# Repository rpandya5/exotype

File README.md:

# Exotype: Intraoral Assistive Speech Device with AR Interface

## Project Overview
Exotype is an assistive speech wearable device combining an intraoral interface with AR-enhanced visual feedback for individuals with severe speech disabilities. This system enables intuitive text input through tongue movements and EMG-based bite detection. This was developed at Founders Inc (San Francisco) as part of the University Residency Program.

Thank you to Merge Grants and 1517's Medici Project for supporting this project!

*This project is still being developed. All files may not be up to date.*

## Demo & Hardware
<div align="center">
  <table>
    <tr>
      <td align="center" width="50%">
        
        <br>
        <em>Project Demo Video</em>
      </td>
      <td align="center" width="50%">
        
        <br>
        <em>Exotype Prototype</em>
      </td>
    </tr>
  </table>
</div>

## Technical Specifications

### Intraoral Interface
- Input Mechanism: Analog thumbstick (Adafruit SWITCH THUMBSTICK PUCK #2765)
  - Dual 10kΩ potentiometer configuration
  - Self-centering mechanism
  - Dimensions: 17.5mm × 17.4mm × 12.0mm
  - X/Y axis voltage output proportional to deflection

### EMG Bite Detection
- Sensor: MyoWare® 2.0 Muscle Sensor
  - Operating Voltage: 2.27V-5.47V (typical 3.3V-5V)
  - Input Bias Current: 250pA (max 1nA)
  - Form Factor: 37.57mm × 35.90mm
  - Triple output modes: Raw EMG/Rectified/Envelope
  - Cheek-mounted electrode configuration
  - Adjustable gain for sensitivity tuning

### Microcontroller System
- Platform: Seeed Studio XIAO ESP32C3
  - Built-in ADC for potentiometer signal processing
  - Bluetooth connectivity for AR glasses interface
  - Power Management:
    - 3.7V LiPo battery configuration
    - Step-up converter

### Visual Interface
- Display: VUF-110 Wearable Display
  - Physical Display: 0.195"
  - Virtual Screen: 4" at 12" viewing distance
  - Resolution: 720p HDMI input
  - Refresh Rate: 60Hz
  - Power: Internal battery (90-minute runtime)
  - Charging: 5V Micro USB
  - Mounting: Magnetic docking system

## PCB Design Specifications
Custom flexible PCB design optimized for intraoral placement:
- Manufacturer Specifications:
  - Single layer polyimide flex construction
  - Thickness: 0.13mm
  - Dimensions: 250mm × 62mm
  - Copper Weight: 0.5oz (18μm)
  - Surface Finish: ENIG (2U")
  - Track/Spacing: ≥0.06mm
  - Minimum Hole Size: ≥φ0.15/0.35mm
  - Coverlay: Black with white silkscreen

<table>
  <tr>
    <td align="center" width="50%">
      
      <br>
      <em>PCB Schematic</em>
    </td>
    <td align="center" width="50%">
      
      <br>
      <em>PCB Layout</em>
    </td>
  </tr>
</table>

## System Architecture & Operation Cycle

### Signal Flow & Processing Pipeline

#### 1. Input Acquisition

**Joystick Processing:**
- Dual 10kΩ potentiometers generate analog voltage signals (0-3.3V) corresponding to X/Y positions
- ESP32C3's integrated 12-bit ADC samples each axis:
  - ADC1 Channel 0: X-axis position
  - ADC1 Channel 1: Y-axis position
- Sampling rate: 100Hz per channel
- Resolution: 4096 discrete positions (12-bit)
- Built-in voltage reference for stable measurements

**EMG Signal Processing:**
- MyoWare 2.0 sensor captures muscle activation during bite events
- Rectified EMG signal processed through envelope detection
- Analog output fed into ESP32C3 ADC Channel 2
- Signal conditioning:
  - Hardware gain adjustment on MyoWare board
  - Digital threshold filtering for bite detection
  - Debouncing to prevent false triggers

#### 2. Power Management
- 3.7V 500mAh LiPo battery
- Voltage monitoring via ESP32C3 ADC
- Power distribution:
  - ESP32C3: 3.3V operating voltage
  - Joystick potentiometers: 3.3V reference
  - EMG sensor: 3.3V regulated supply

#### 3. Data Processing & Communication

**Microcontroller Operations:**
- ESP32C3 core functions:
  - ADC sampling management
  - Digital filtering of input signals
  - Coordinate mapping for cursor position
  - Bluetooth packet formation and transmission
  - Power state management

**Bluetooth Communication Protocol:**
- BLE 5.0 implementation
- Custom GATT service for device communication
- Packet structure:
```
{
  timestamp: uint32,
  x_pos: uint12,
  y_pos: uint12,
  bite_state: bool,
  battery_level: uint8
}
```
- Transmission rate: 50Hz
- Error checking and packet validation
- Auto-reconnection handling

#### 4. Visual Interface System

**Display Processing:**
- HDMI signal generation (720p @ 60Hz)
- Virtual keyboard overlay:
  - Resolution: 1280x720
  - Dynamic keyboard layout adaptation
  - Visual feedback for cursor position
  - Character highlighting on hover

**Cursor Control System:**
- Non-linear acceleration mapping for precise control
- Coordinate transformation:
```
x_screen = f(x_joystick) * screen_width
y_screen = f(y_joystick) * screen_height
```
where f(x) implements smooth acceleration curve

#### 5. Text Input & Processing

**Selection System:**
- Character selection confirmation delay: 50ms
- Double-bite detection for special functions

**Text Prediction Engine:**
- N-gram based prediction model
- Personal dictionary integration
- Context-aware suggestions
- Update frequency: Real-time on character input

<p align="center">
  
  <br>
  <em>Keyboard display on AR Glasses</em>
</p>

### Data Flow Diagram
```mermaid
graph TD
    A[Joystick Input] -->|Analog Voltage| B[ADC Conversion]
    C[EMG Sensor] -->|Envelope Signal| B
    B --> D[ESP32C3 Processing]
    D -->|BLE Protocol| E[Display System]
    D -->|Power Management| F[Battery Monitor]
    E --> G[Keyboard Overlay]
    E --> H[Text Prediction]
    G --> I[Visual Feedback]
    H --> I
```

## Future Development Roadmap
1. Integration with Brilliant Labs' Frame AR glasses
2. Capacitive touch sensor implementation
3. Custom AR glasses development
4. Enhanced predictive text algorithms
5. Extended battery life optimizations

## Repository Structure
```
├── firmware/
│   ├── src/
│   │   ├── main.cpp
│   │   ├── mouse_control.py
│   │   └── test.py
│   └── platformio.ini
├── hardware/
│   ├── pcb/
│   │   ├── gerbers/
│   │   └── kicad_files/
│   └── ar-glasses/ (to be completed)
├── software/
    ├── t_complete.py
    └── t_keyboard.py

```

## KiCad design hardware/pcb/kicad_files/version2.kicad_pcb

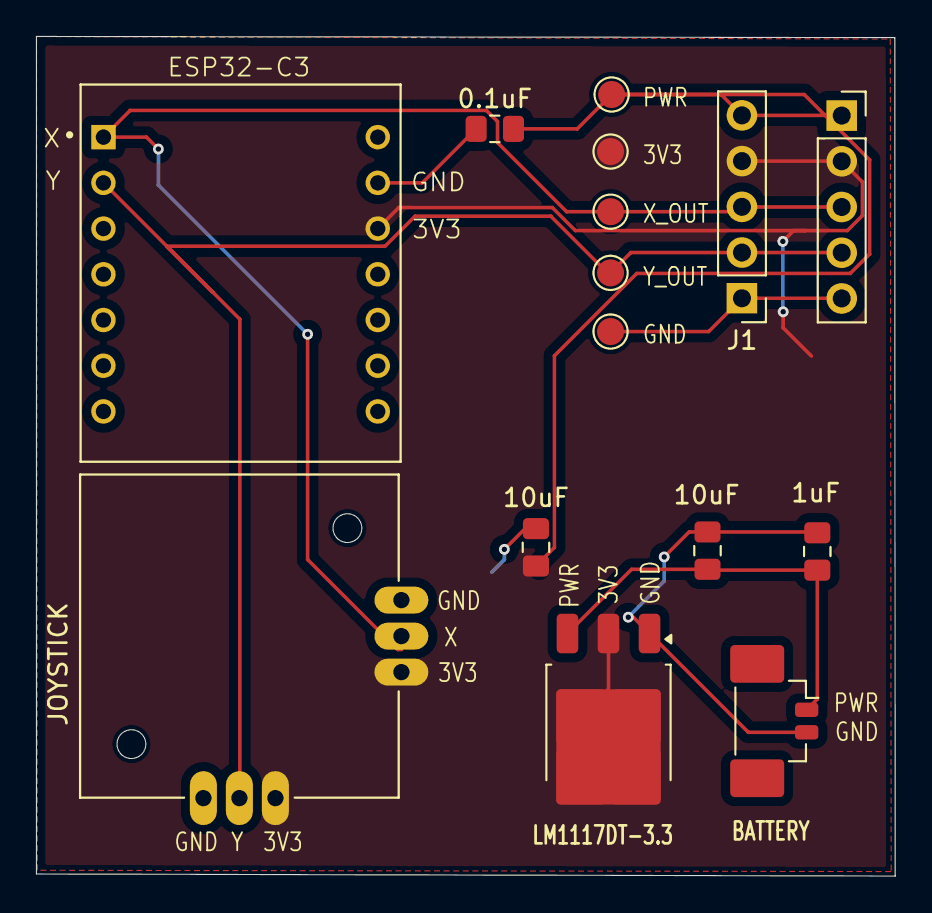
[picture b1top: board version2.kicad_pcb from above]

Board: 2 copper layers, 47.7 x 46.6 mm, 15 parts (0 on the bottom side), 5 nets.

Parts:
BATTERY: BATTERY; Molex_PicoBlade_53398-0271_1x02-1MP_P1.25mm_Vertical
C1: 1uF; C_0805_2012Metric_Pad1.18x1.45mm_HandSolder
C2, C3: 10uF; C_0805_2012Metric_Pad1.18x1.45mm_HandSolder
C4: 0.1uF; C_0805_2012Metric_Pad1.18x1.45mm_HandSolder
J1: Conn_01x05_Pin; PinHeader_1x05_P2.54mm_Vertical
J2: Conn_01x05_Socket; PinSocket_1x05_P2.54mm_Vertical
JOYSTICK: 2765; SW_2765
TP1: PWR; TestPoint_Pad_D1.5mm
TP2: 3.3V; TestPoint_Pad_D1.5mm
TP3: GND; TestPoint_Pad_D1.5mm
TP4: X_OUT; TestPoint_Pad_D1.5mm
TP5: Y_OUT; TestPoint_Pad_D1.5mm
U1: LM1117DT-3.3; TO-252-3_TabPin2
U2: 113991054; MODULE_113991054

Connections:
/3.3V: C2.1, J1.4, J2.2, JOYSTICK.X+, JOYSTICK.Y+, TP2.1, U1.2 (VO), U2.12 (VCC_3V3)
/PWR: BATTERY.1 (+), C1.1, C3.1, C4.1, J1.5, J2.1, TP1.1, U1.3 (VI)
/X_OUT: J1.3, J2.3, JOYSTICK.X, TP4.1, U2.1 (D0)
/Y_OUT: J1.2, J2.4, JOYSTICK.Y, TP5.1, U2.2 (D1)
GND: BATTERY.2 (-), C1.2, C2.2, C3.2, C4.2, J1.1, J2.5, JOYSTICK.X-, JOYSTICK.Y-, TP3.1, U1.1 (GND), U2.13 (GND)

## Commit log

2024-11-01 Create gerber_drill_files
2024-11-01 Create file
